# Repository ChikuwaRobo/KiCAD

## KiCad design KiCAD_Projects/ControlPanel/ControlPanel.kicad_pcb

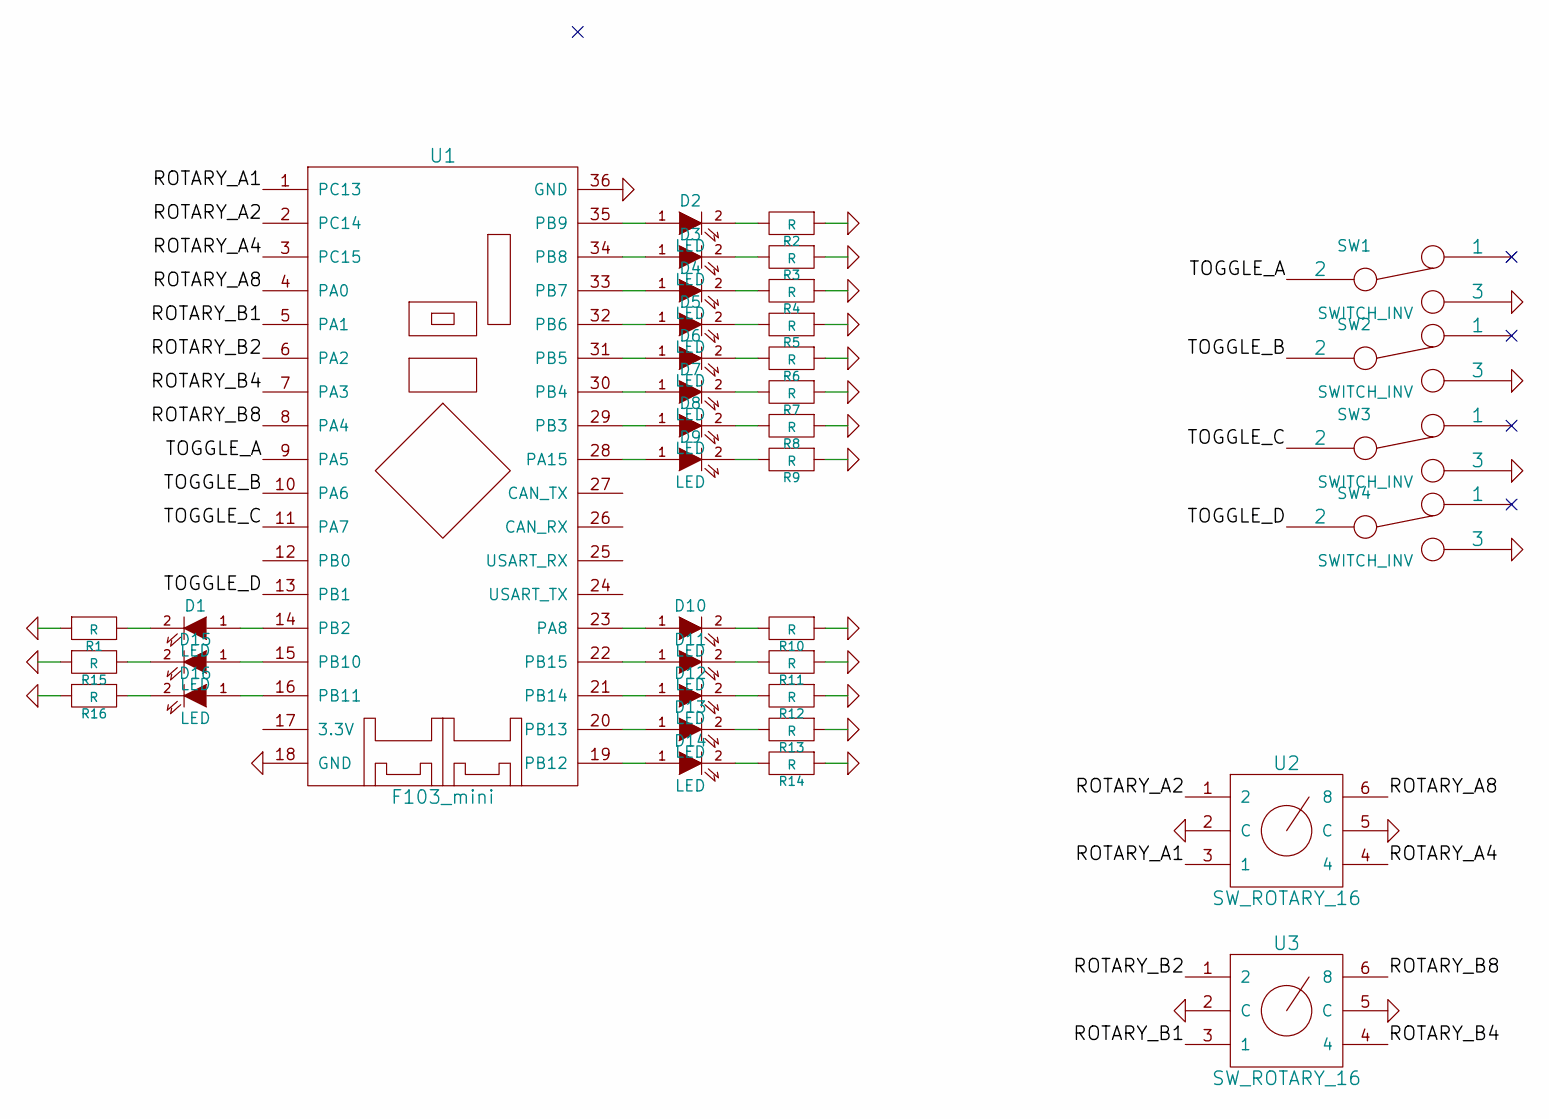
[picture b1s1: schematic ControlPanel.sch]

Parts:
D1, D2, D3, D4, D5, D6, D7, D8, D9, D10, D11, D12, D13, D14, D15, D16: LED; LED-3MM
R1, R2, R3, R4, R5, R6, R7, R8, R9, R10, R11, R12, R13, R14, R15, R16: R; C1608_WP
SW1, SW2, SW3, SW4: SWITCH_INV; SW_toggle_3P
U1: F103_mini
U2, U3: SW_ROTARY_16; rotary_0F

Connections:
/ROTARY_A1: U1.1 (PC13), U2.3 (1)
/ROTARY_A2: U1.2 (PC14), U2.1 (2)
/ROTARY_A4: U1.3 (PC15), U2.4
/ROTARY_A8: U1.4 (PA0), U2.6 (8)
/ROTARY_B1: U1.5 (PA1), U3.3 (1)
/ROTARY_B2: U1.6 (PA2), U3.1 (2)
/ROTARY_B4: U1.7 (PA3), U3.4
/ROTARY_B8: U1.8 (PA4), U3.6 (8)
/TOGGLE_A: SW1.2, U1.9 (PA5)
/TOGGLE_B: SW2.2, U1.10 (PA6)
/TOGGLE_C: SW3.2, U1.11 (PA7)
/TOGGLE_D: SW4.2, U1.13 (PB1)
GND: R1.1, R2.1, R3.1, R4.1, R5.1, R6.1, R7.1, R8.1, R9.1, R10.1, R11.1, R12.1, R13.1, R14.1, R15.1, R16.1, SW1.3, SW2.3, SW3.3, SW4.3, U1.18 (GND), U1.36 (GND), U2.2 (C), U2.5 (C), U3.2 (C), U3.5 (C)
unnamed: D1.1 (A), U1.14 (PB2)
unnamed: D1.2 (K), R1.2
unnamed: D2.1 (A), U1.35 (PB9)
unnamed: D2.2 (K), R2.2
unnamed: D3.1 (A), U1.34 (PB8)
unnamed: D3.2 (K), R3.2
unnamed: D4.1 (A), U1.33 (PB7)
unnamed: D4.2 (K), R4.2
unnamed: D5.1 (A), U1.32 (PB6)
unnamed: D5.2 (K), R5.2
unnamed: D6.1 (A), U1.31 (PB5)
unnamed: D6.2 (K), R6.2
unnamed: D7.1 (A), U1.30 (PB4)
unnamed: D7.2 (K), R7.2
unnamed: D8.1 (A), U1.29 (PB3)
unnamed: D8.2 (K), R8.2
unnamed: D9.1 (A), U1.28 (PA15)
unnamed: D9.2 (K), R9.2
unnamed: D10.1 (A), U1.23 (PA8)
unnamed: D10.2 (K), R10.2
unnamed: D11.1 (A), U1.22 (PB15)
unnamed: D11.2 (K), R11.2
unnamed: D12.1 (A), U1.21 (PB14)
unnamed: D12.2 (K), R12.2
unnamed: D13.1 (A), U1.20 (PB13)
unnamed: D13.2 (K), R13.2
unnamed: D14.1 (A), U1.19 (PB12)
unnamed: D14.2 (K), R14.2
unnamed: D15.1 (A), U1.15 (PB10)
unnamed: D15.2 (K), R15.2
unnamed: D16.1 (A), U1.16 (PB11)
unnamed: D16.2 (K), R16.2

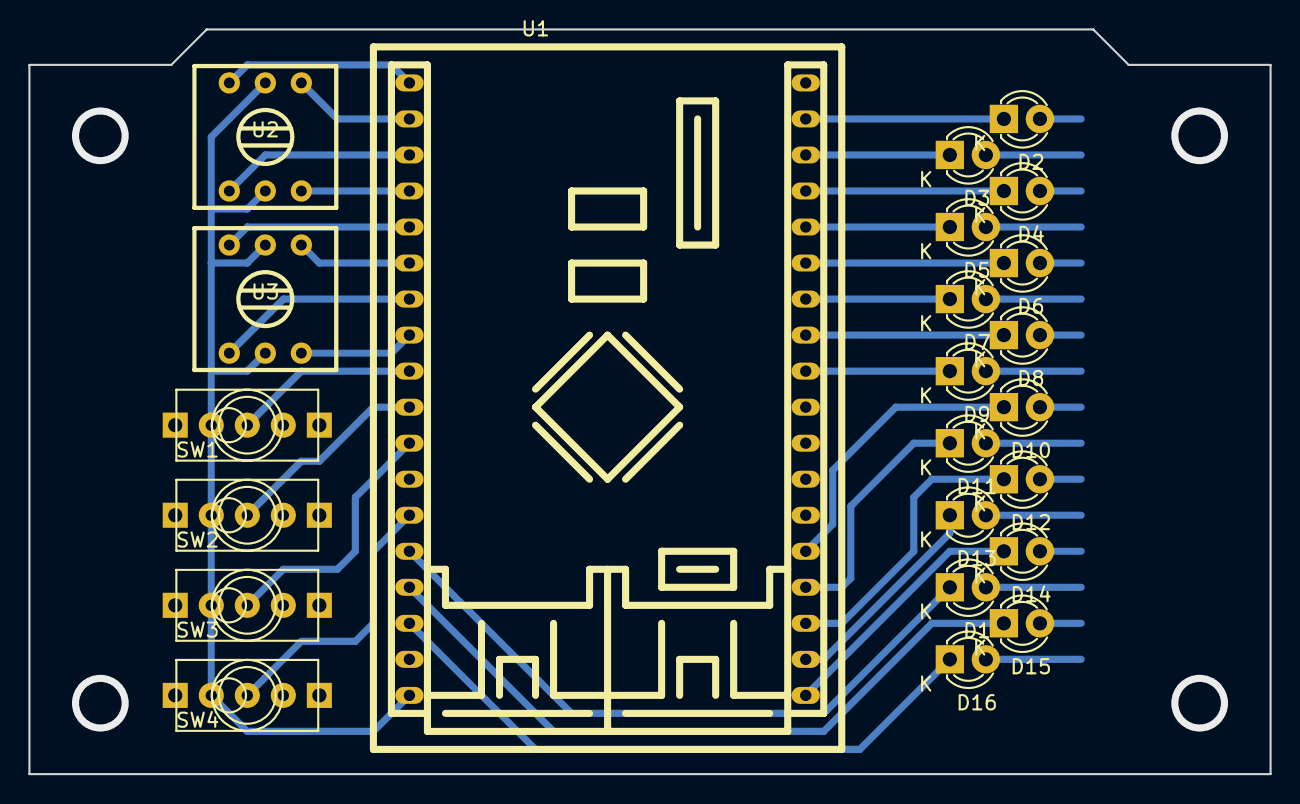
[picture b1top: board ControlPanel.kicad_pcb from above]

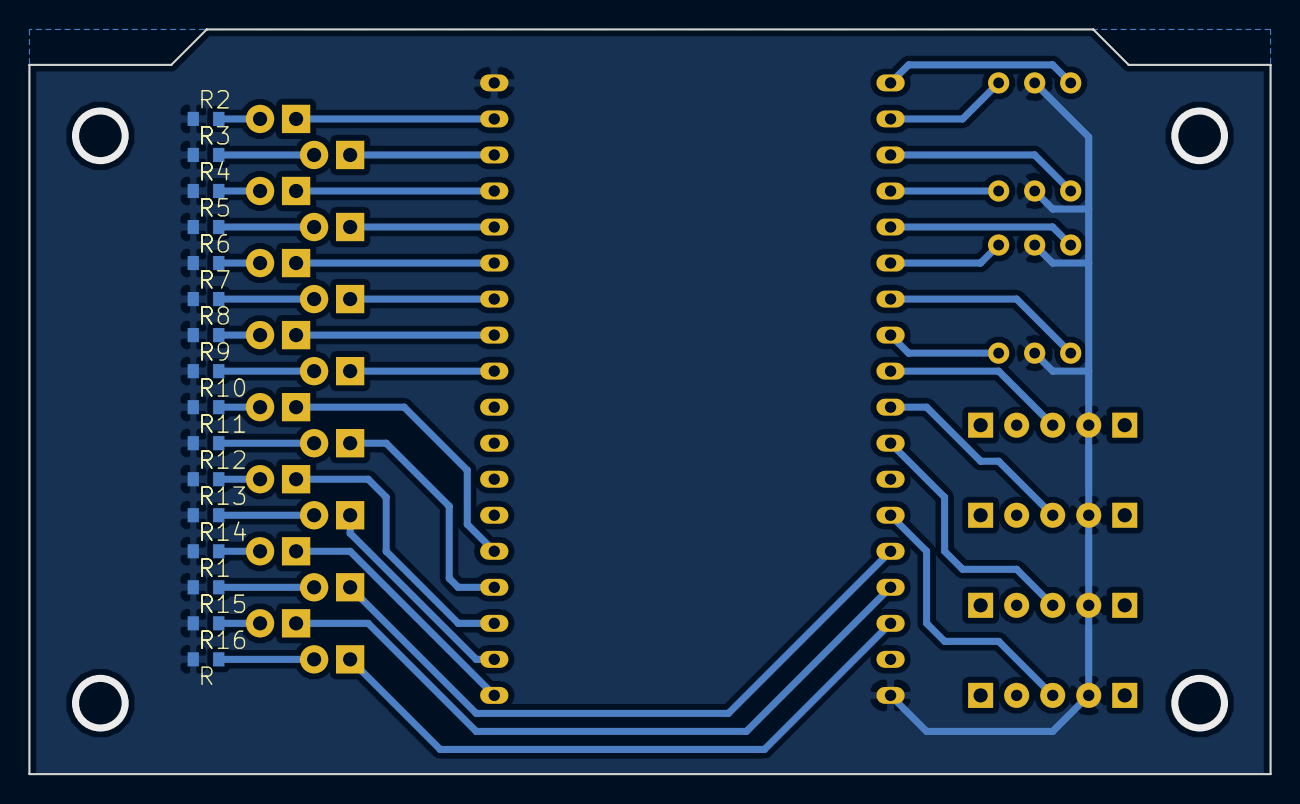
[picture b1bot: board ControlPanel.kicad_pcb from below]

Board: 2 copper layers, 87.5 x 52.5 mm, 39 parts (16 on the bottom side), 45 nets.

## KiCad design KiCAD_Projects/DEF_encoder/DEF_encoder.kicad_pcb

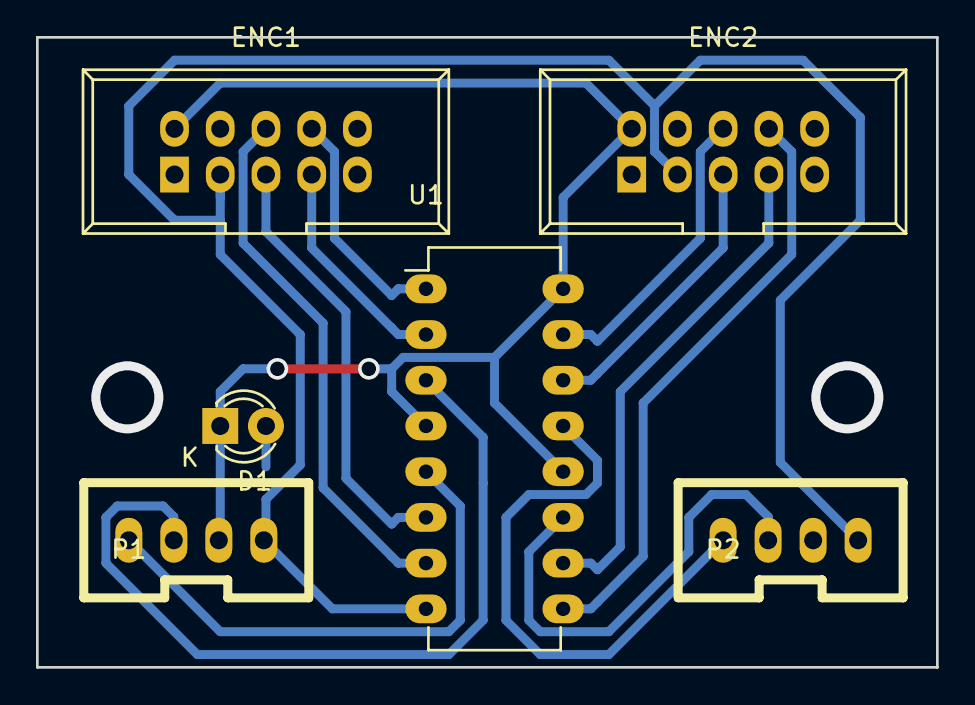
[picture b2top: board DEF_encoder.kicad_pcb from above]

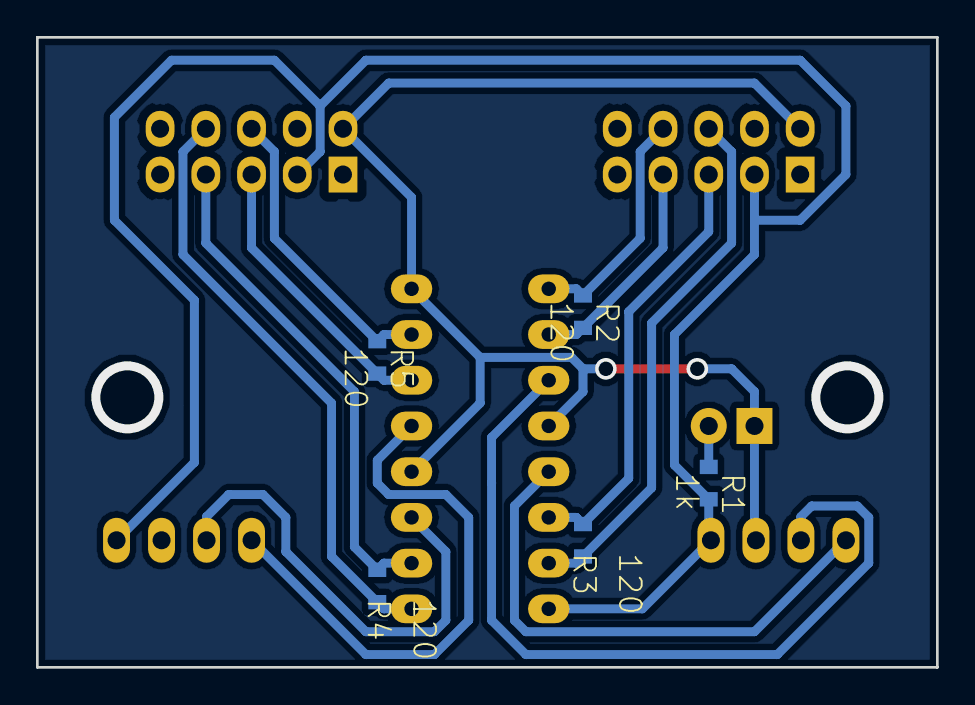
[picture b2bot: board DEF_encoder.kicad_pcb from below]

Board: 2 copper layers, 50.0 x 35.0 mm, 11 parts (5 on the bottom side), 15 nets.

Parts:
D1: LED; LED-3MM
ENC1, ENC2: RS422_ENCODER; DEF_ENCODER
P1, P2: CONN_01X04; XA_4T
R1: 1k; C1608_WP
R2, R3, R4, R5: 120; C1608_WP
U1: SN75175; DIP-16_W7.62mm_LongPads

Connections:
+5V: D1.1, ENC1.2, ENC2.2, P1.2, P2.2, U1.4, U1.12, U1.16
/IN1_AA: ENC1.7, R2.2, U1.2
/IN1_AB: ENC1.8, R2.1, U1.1
/IN1_BA: ENC1.5, R3.2, U1.6
/IN1_BB: ENC1.6, R3.1, U1.7
/IN2_AA: ENC2.7, R4.2, U1.10
/IN2_AB: ENC2.8, R4.1, U1.9
/IN2_BA: ENC2.5, R5.2, U1.14
/IN2_BB: ENC2.6, R5.1, U1.15
/OUT1_A: P1.3, U1.3
/OUT1_B: P1.4, U1.5
/OUT2_A: P2.3, U1.11
/OUT2_B: P2.4, U1.13
GND: ENC1.3, ENC2.3, P1.1, P2.1, R1.2, U1.8
unnamed: D1.2, R1.1

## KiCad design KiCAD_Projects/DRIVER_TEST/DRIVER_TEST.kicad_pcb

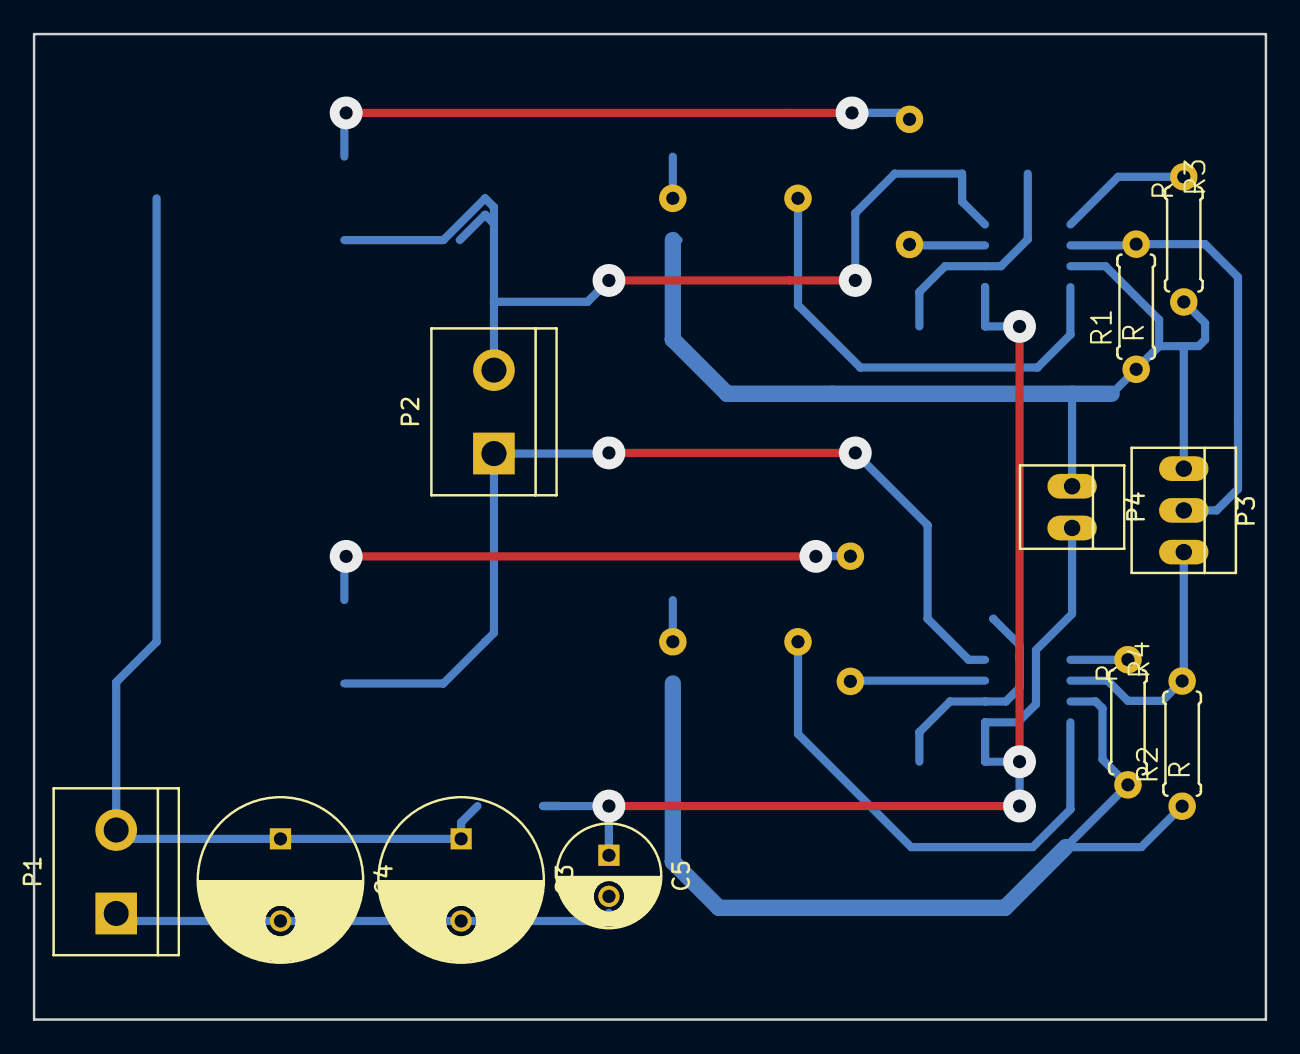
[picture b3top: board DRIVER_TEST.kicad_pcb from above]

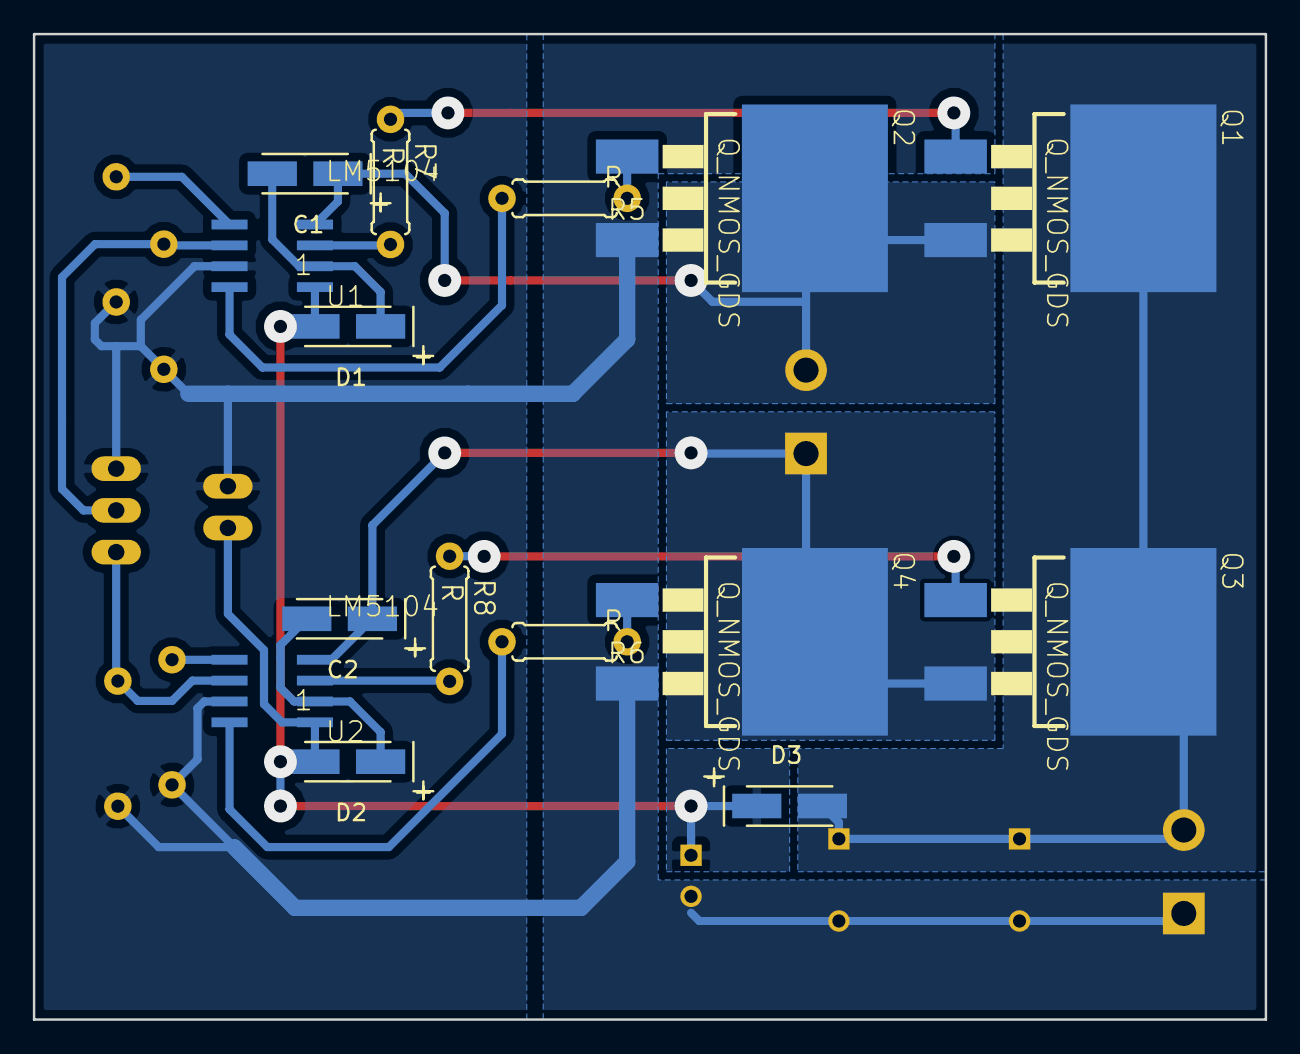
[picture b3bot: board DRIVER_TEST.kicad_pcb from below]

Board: 2 copper layers, 75.0 x 60.0 mm, 26 parts (15 on the bottom side), 19 nets.

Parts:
C1, C2: C; TantalC_SizeA_EIA-3216_HandSoldering
C3, C4: C; C_Radial_D10_L25_P5
C5: C; C_Radial_D6.3_L11.2_P2.5
D1, D2, D3: D; TantalC_SizeA_EIA-3216_HandSoldering
P1, P2: CONN_01X02; bornier2
P3: CONN_01X03; PINHEAD1-3
P4: CONN_01X02; PINHEAD1-2
Q1, Q2, Q3, Q4: Q_NMOS_GDS; D2PACK
R1, R2, R3, R4, R5, R6, R7, R8: R; 0207%2f7
U1, U2: LM5104; SOP08

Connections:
+15V: C5.1, D1.2, D2.2, D3.1, P4.2, U1.1, U2.1
+BATT: C3.1, C4.1, D3.2, P1.2, Q1.2, Q3.2
GND: C3.2, C4.2, C5.2, P1.1, P3.1, P4.1, Q2.3, Q4.3, R1.1, R2.1, R3.2, R4.2, U1.7, U2.7
IN0: P3.3, R2.2, U2.6
IN1: P3.2, R1.2, U1.6
unnamed: C1.2, D1.1, U1.2
unnamed: C2.2, D2.1, U2.2
unnamed: Q1.1, R7.1
unnamed: Q2.1, R5.1
unnamed: Q3.1, R8.1
unnamed: Q4.1, R6.1
unnamed: R3.1, U1.5
unnamed: R4.1, U2.5
unnamed: R5.2, U1.8
unnamed: R6.2, U2.8
unnamed: R7.2, U1.3
unnamed: R8.2, U2.3
OUT0: C2.1, P2.1, Q3.3, Q4.2, U2.4
OUT1: C1.1, P2.2, Q1.3, Q2.2, U1.4

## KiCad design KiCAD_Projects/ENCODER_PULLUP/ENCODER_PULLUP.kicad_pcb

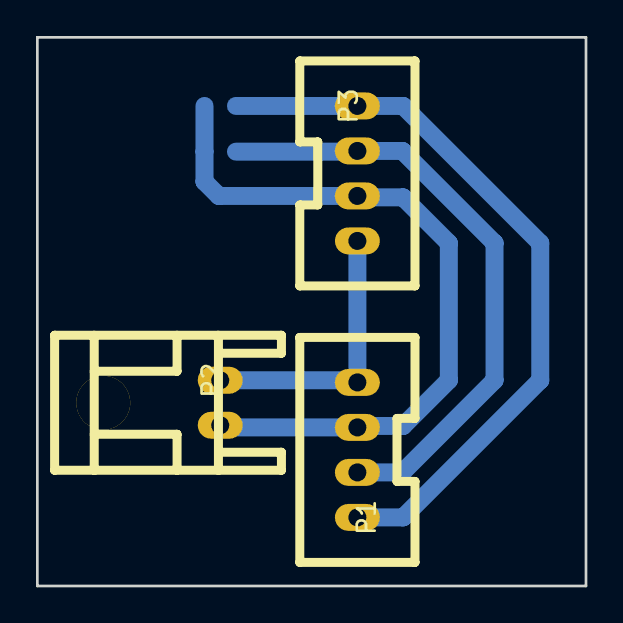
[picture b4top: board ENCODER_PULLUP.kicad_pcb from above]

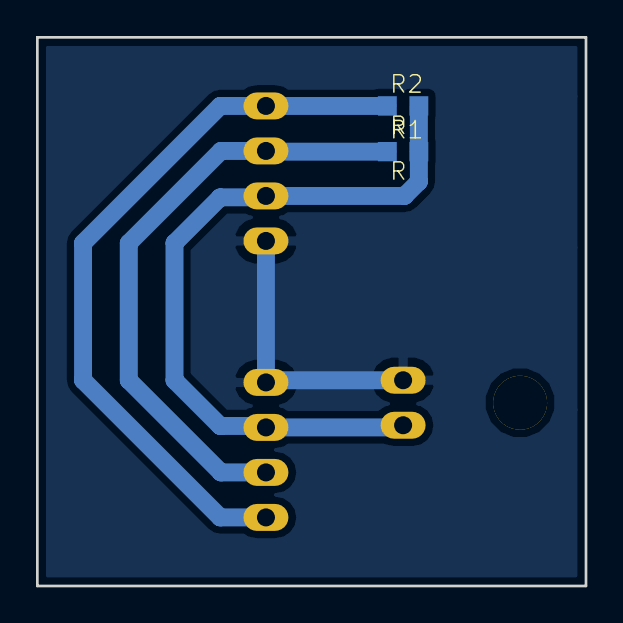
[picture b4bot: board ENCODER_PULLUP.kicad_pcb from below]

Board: 2 copper layers, 30.5 x 30.5 mm, 5 parts (2 on the bottom side), 4 nets.

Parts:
P1, P3: CONN_01X04; XA_4T
P2: CONN_01X02; XA_2LC
R1, R2: R; C0603K

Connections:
+5V: P1.2, P2.2, P3.2, R1.2, R2.2
GND: P1.1, P2.1, P3.1
unnamed: P1.3, P3.3, R1.1
unnamed: P1.4, P3.4, R2.1

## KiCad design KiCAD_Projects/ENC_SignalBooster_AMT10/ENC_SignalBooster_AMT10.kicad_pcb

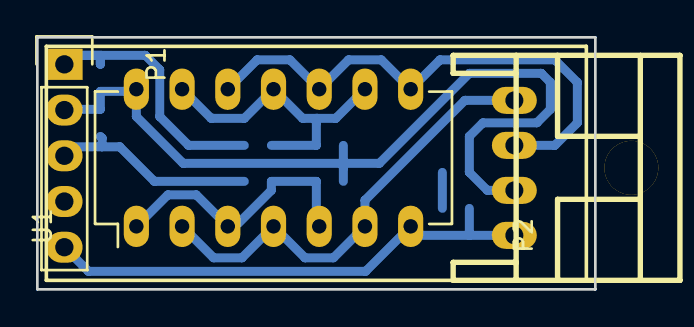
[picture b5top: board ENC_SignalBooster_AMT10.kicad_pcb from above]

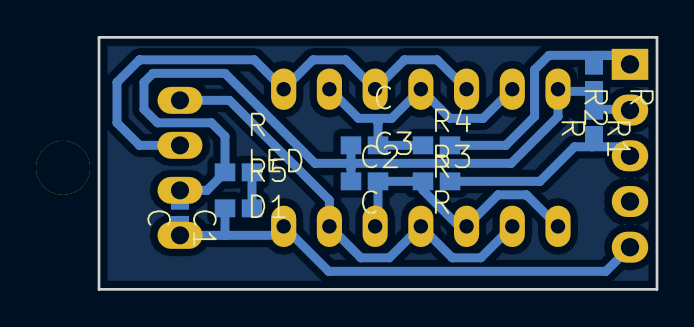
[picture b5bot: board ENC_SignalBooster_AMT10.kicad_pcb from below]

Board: 2 copper layers, 31.0 x 14.0 mm, 12 parts (9 on the bottom side), 9 nets.

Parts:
C1, C2, C3: C; C1608_NP
D1: LED; C1608_NP
P1: CONN_01X05; Socket_Strip_Straight_1x05
P2: CONN_01X04; XA_4LC
R1, R2, R3, R4, R5: R; C1608_NP
U1: 74HC04; DIP-14_W7.62mm_LongPads

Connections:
+5V: C1.1, C2.1, C3.2, P1.2, P2.2, R1.1, R2.1, R5.2, U1.14
/ENC_A: P1.3, R1.2, R3.2
/ENC_B: P1.1, R2.2, R4.2
/OUT_A: P2.4, U1.2, U1.4, U1.6
/OUT_B: P2.3, U1.8, U1.10, U1.12
GND: C1.2, D1.2, P1.5, P2.1, U1.7
unnamed: C2.2, R3.1, U1.1, U1.3, U1.5
unnamed: C3.1, R4.1, U1.9, U1.11, U1.13
unnamed: D1.1, R5.1

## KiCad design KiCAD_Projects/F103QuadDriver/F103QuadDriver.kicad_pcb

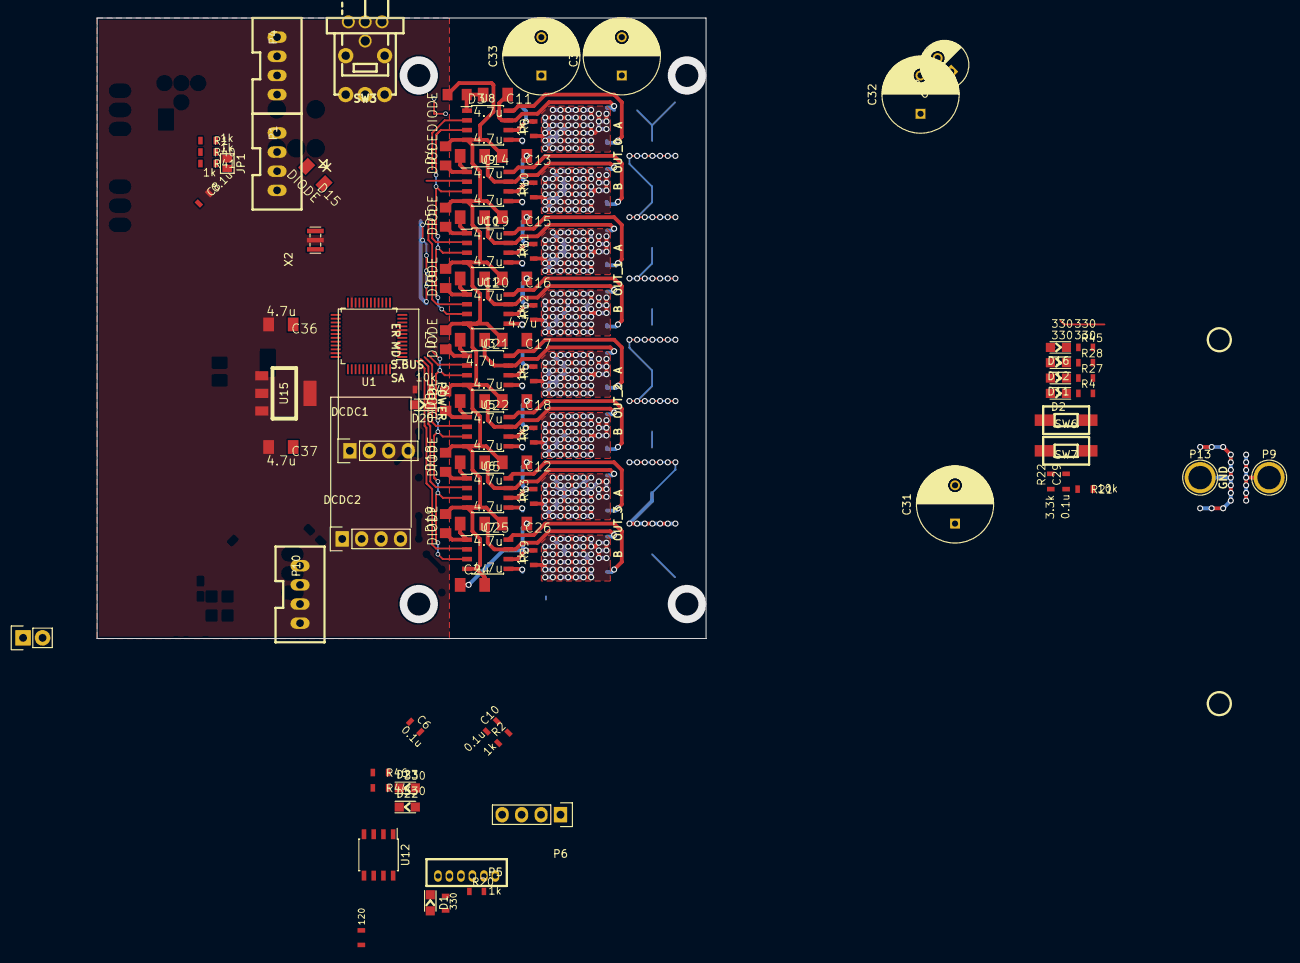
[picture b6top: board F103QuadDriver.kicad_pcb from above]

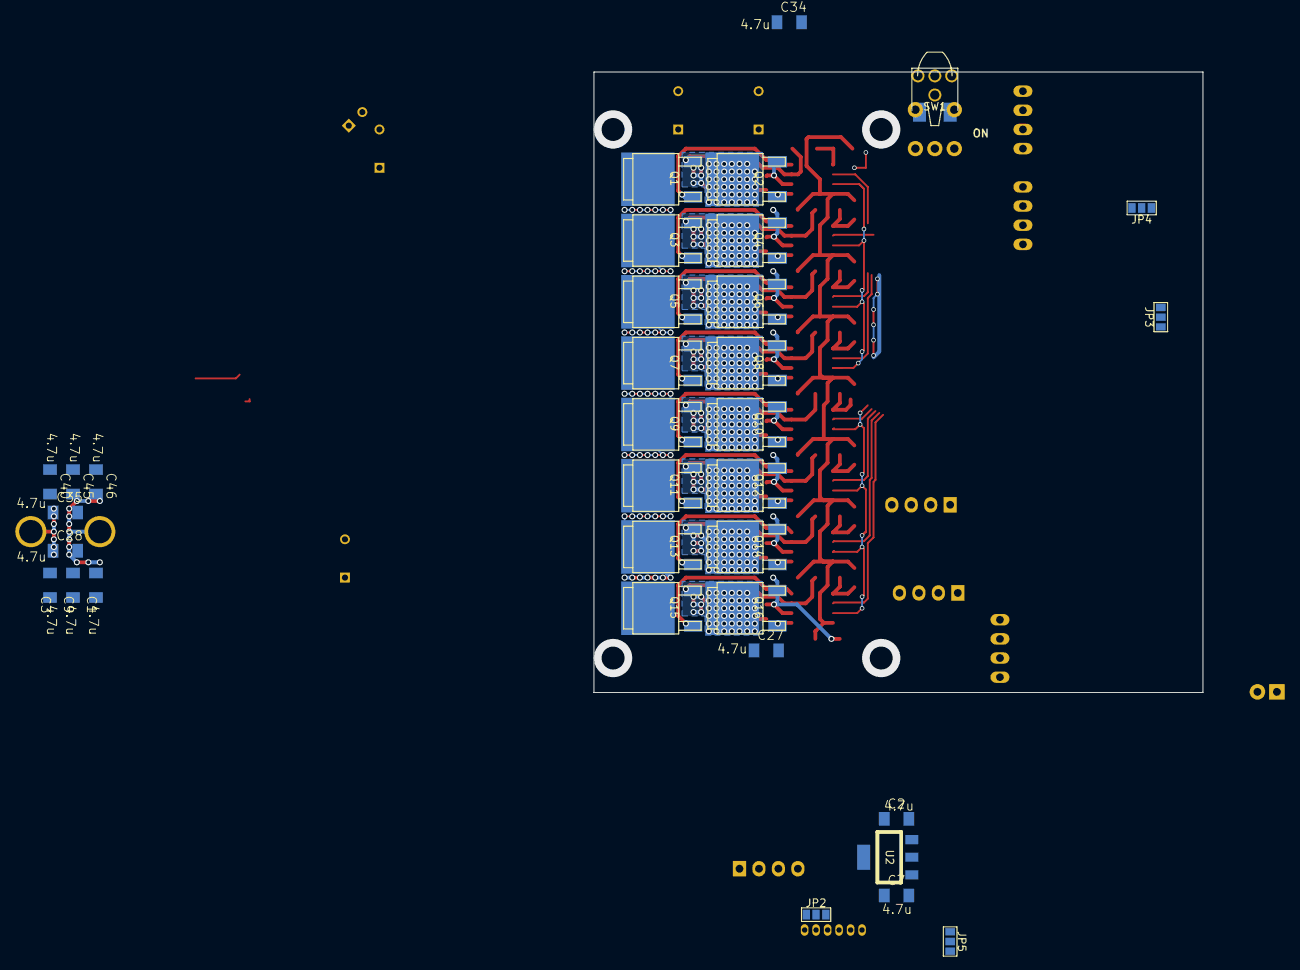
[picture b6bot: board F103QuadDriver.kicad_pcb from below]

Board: 2 copper layers, 79.5 x 81.0 mm, 129 parts (34 on the bottom side), 88 nets.

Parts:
C1, C2, C3, C5, C7, C9, C11, C12, C13, C14, C15, C16, C17, C18, C19, C20, C21, C22, C24, C25, C26, C27, C28, C34, C35, C36, C37, C40, C45, C46: 4.7u; C3216_S
C6, C8, C10, C29: 0.1u; C1608_WP_S
C23: C; C_Radial_D6.3_L11.2_P2.5
C30, C31, C32, C33: 220u; C_Radial_D10_L13_P5
D1, D2, D11, D12, D16, D20, D22, D23: LED; LED_0805
D3, D4, D5, D6, D7, D8, D18, D19: DIODE; C2012
D15: DIODE; C3216_S
DCDC1, DCDC2: ChinaDC-DC
JP1: JUMPER; GS2
JP2, JP3, JP4, JP5: JUMPER3; GS3
P1, P4, P10: CONN_01X04; XA_4T
P5: CONN_01X06; ZH_6T
P6: CONN_01X04; Socket_Strip_Straight_1x04
P9, P13: CONN_01X01; 1pin
P11: CONN_01X02; Pin_Header_Straight_1x02
P19: CONN_01X01; KawaRobo_Headsink_95x35
Q1, Q2, Q3, Q4, Q5, Q6, Q7, Q8, Q9, Q10, Q11, Q12, Q13, Q14, Q15, Q16: MOSFET_N; SOT-428_GDS_compact
R1, R2, R5, R6, R9, R10, R11, R12, R13, R20, R29, R40, R41: 1k; C1608_WP_S
R3, R4, R27, R28, R44, R45, R46: 330; C1608_WP_S
R21, R42: 10k; C1608_WP_S
R22: 3.3k; C1608_WP_S
R30: 120; C1608_WP_S
SW1: SW_PUSH; ESE22MH
SW3: SWITCH_INV; RSpro_slide_side
SW6, SW7: SW_PUSH; RP_SMD_Button
U1: STM32F103_48; LQFP-48_7x7mm_Pitch0.5mm
U2: NCP1117ST33T3G; SOT-223_reg
U3, U5, U6, U7, U8, U9, U10, U11: NCP5359; SOIC-8_3.9x4.9mm_Pitch1.27mm_S
U12: MAX3051; SOIC-8_3.9x4.9mm_Pitch1.27mm_S
U15: NCP1117ST12T3G; SOT-223_reg
X2: ceralock; Resonator_3×1.3mm

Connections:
+3.3V: C6.2, C7.1, C8.2, C10.2, D1.1, JP2.3, JP3.3, JP4.3, R1.1, R40.1, R41.1, U1.1, U1.9, U1.24, U1.36, U1.48, U2.2, U12.3
+5V: C2.1, DCDC1.4, JP2.1, JP3.1, JP4.1, JP5.1, P6.1, U2.3
+12V: DCDC2.4, JP5.3
+BATT: C1.1, C3.1, C9.1, C27.1, C28.1, C30.1, C31.1, C32.1, C33.1, C34.1, C35.1, C40.1, C45.1, C46.1, D20.1, P9.1, Q1.D, Q3.D, Q5.D, Q7.D, Q9.D, Q11.D, Q13.D, Q15.D, R21.1, SW3.2
/AIN_1: P1.3, U1.14
/AIN_2: P1.4, U1.15
/BOOT0: R2.2, U1.44
/CAN_H: P10.3, R30.1, U12.7
/CAN_L: P10.4, P11.2, U12.6
/CAN_RX: U1.32, U12.4
/CAN_TX: U1.33, U12.1
/GD_12V: C12.2, C13.2, C15.2, C16.2, C17.2, C18.2, C24.2, C26.2, C37.1, D3.2, D4.2, D5.2, D6.2, D7.2, D8.2, D18.2, D19.2, U3.4, U5.4, U6.4, U7.4, U8.4, U9.4, U10.4, U11.4, U15.2
/LOGIC_BATT: C23.2, C36.1, D15.1, DCDC1.2, DCDC2.2, U15.3
/NRST: R1.2, SW1.2, U1.7
/OSC_IN: U1.5, X2.1
/OSC_OUT: U1.6, X2.3
/OUT_0_A: C11.1, Q1.S, Q2.D, R9.1, U8.7
/OUT_0_B: C14.1, Q3.S, Q4.D, R10.1, U9.7
/OUT_1_A: C19.1, Q5.S, Q6.D, R11.1, U10.7
/OUT_1_B: C20.1, Q7.S, Q8.D, R12.1, U11.7
/OUT_2_A: C21.1, Q9.S, Q10.D, R5.1, U3.7
/OUT_2_B: C22.1, Q11.S, Q12.D, R6.1, U5.7
/OUT_3_A: C5.1, Q13.S, Q14.D, R13.1, U6.7
/OUT_3_B: C25.1, Q15.S, Q16.D, R29.1, U7.7
/POT_1: P4.3, R40.2, U1.10
/POT_2: P4.4, R41.2, U1.11
/PWM_0_A: U1.19, U8.2
/PWM_0_B: U1.18, U9.2
/PWM_1_A: U1.17, U10.2
/PWM_1_B: U1.16, U11.2
/PWM_2_A: U1.46, U3.2
/PWM_2_B: U1.45, U5.2
/PWM_3_A: U1.43, U6.2
/PWM_3_B: U1.42, U7.2
/STM_LED1: D2.1, U1.2
/STM_LED2: D11.1, U1.3
/STM_LED3: D12.1, U1.4
/STM_LED5: D22.1, U1.39
/STM_LED6: D23.1, U1.38
/STM_SW1: SW6.2, U1.41
/STM_SW2: SW7.2, U1.40
/SWCLK: P5.3, U1.37
/SWDIO: P5.4, U1.34
/USART_RX: P5.6, R20.1, U1.31
/USART_TX: P5.5, P6.4, U1.30
/batt_voltage: C29.1, R21.2, R22.1, U1.12
/~SD: U1.29, U3.3, U5.3, U6.3, U7.3, U8.3, U9.3, U10.3, U11.3
GND: C2.2, C6.1, C7.2, C8.1, C10.1, C23.1, C29.2, C36.2, C37.2, DCDC1.3, DCDC2.3, JP1.1, P1.1, P4.1, P5.1, P6.2, P10.1, R2.1, R3.2, R4.2, R22.2, R27.2, R28.2, R42.2, R44.2, R45.2, R46.2, SW1.1, SW6.1, SW7.1, U1.8, U1.23, U1.35, U1.47, U2.1, U12.2, U12.5, U12.8, U15.1, X2.2
GNDPWR: C1.2, C3.2, C9.2, C12.1, C13.1, C15.1, C16.1, C17.1, C18.1, C24.1, C26.1, C27.2, C28.2, C30.2, C31.2, C32.2, C33.2, C34.2, C35.2, C40.2, C45.2, C46.2, P13.1, Q2.S, Q4.S, Q6.S, Q8.S, Q10.S, Q12.S, Q14.S, Q16.S, R5.2, R6.2, R9.2, R10.2, R11.2, R12.2, R13.2, R29.2, U3.6, U5.6, U6.6, U7.6, U8.6, U9.6, U10.6, U11.6
unnamed: C5.2, D18.1, U6.1
unnamed: C11.2, D3.1, U8.1
unnamed: C14.2, D4.1, U9.1
unnamed: C19.2, D5.1, U10.1
unnamed: C20.2, D6.1, U11.1
unnamed: C21.2, D7.1, U3.1
unnamed: C22.2, D8.1, U5.1
unnamed: C25.2, D19.1, U7.1
unnamed: D1.2, R3.1
unnamed: D2.2, R4.1
unnamed: D11.2, R27.1
unnamed: D12.2, R28.1
unnamed: D15.2, SW3.3
unnamed: D16.2, R45.1
unnamed: D20.2, R42.1
unnamed: D22.2, R44.1
unnamed: D23.2, R46.1
unnamed: JP2.2, P5.2
unnamed: JP3.2, P1.2
unnamed: JP4.2, P4.2
unnamed: JP5.2, P10.2
unnamed: P6.3, R20.2
unnamed: P11.1, R30.2
unnamed: Q1.G, U8.8
unnamed: Q2.G, U8.5
unnamed: Q3.G, U9.8
unnamed: Q4.G, U9.5
unnamed: Q5.G, U10.8
unnamed: Q6.G, U10.5
unnamed: Q7.G, U11.8
unnamed: Q8.G, U11.5
unnamed: Q9.G, U3.8
unnamed: Q10.G, U3.5
unnamed: Q11.G, U5.8
unnamed: Q12.G, U5.5
unnamed: Q13.G, U6.8
unnamed: Q14.G, U6.5
unnamed: Q15.G, U7.8
unnamed: Q16.G, U7.5
